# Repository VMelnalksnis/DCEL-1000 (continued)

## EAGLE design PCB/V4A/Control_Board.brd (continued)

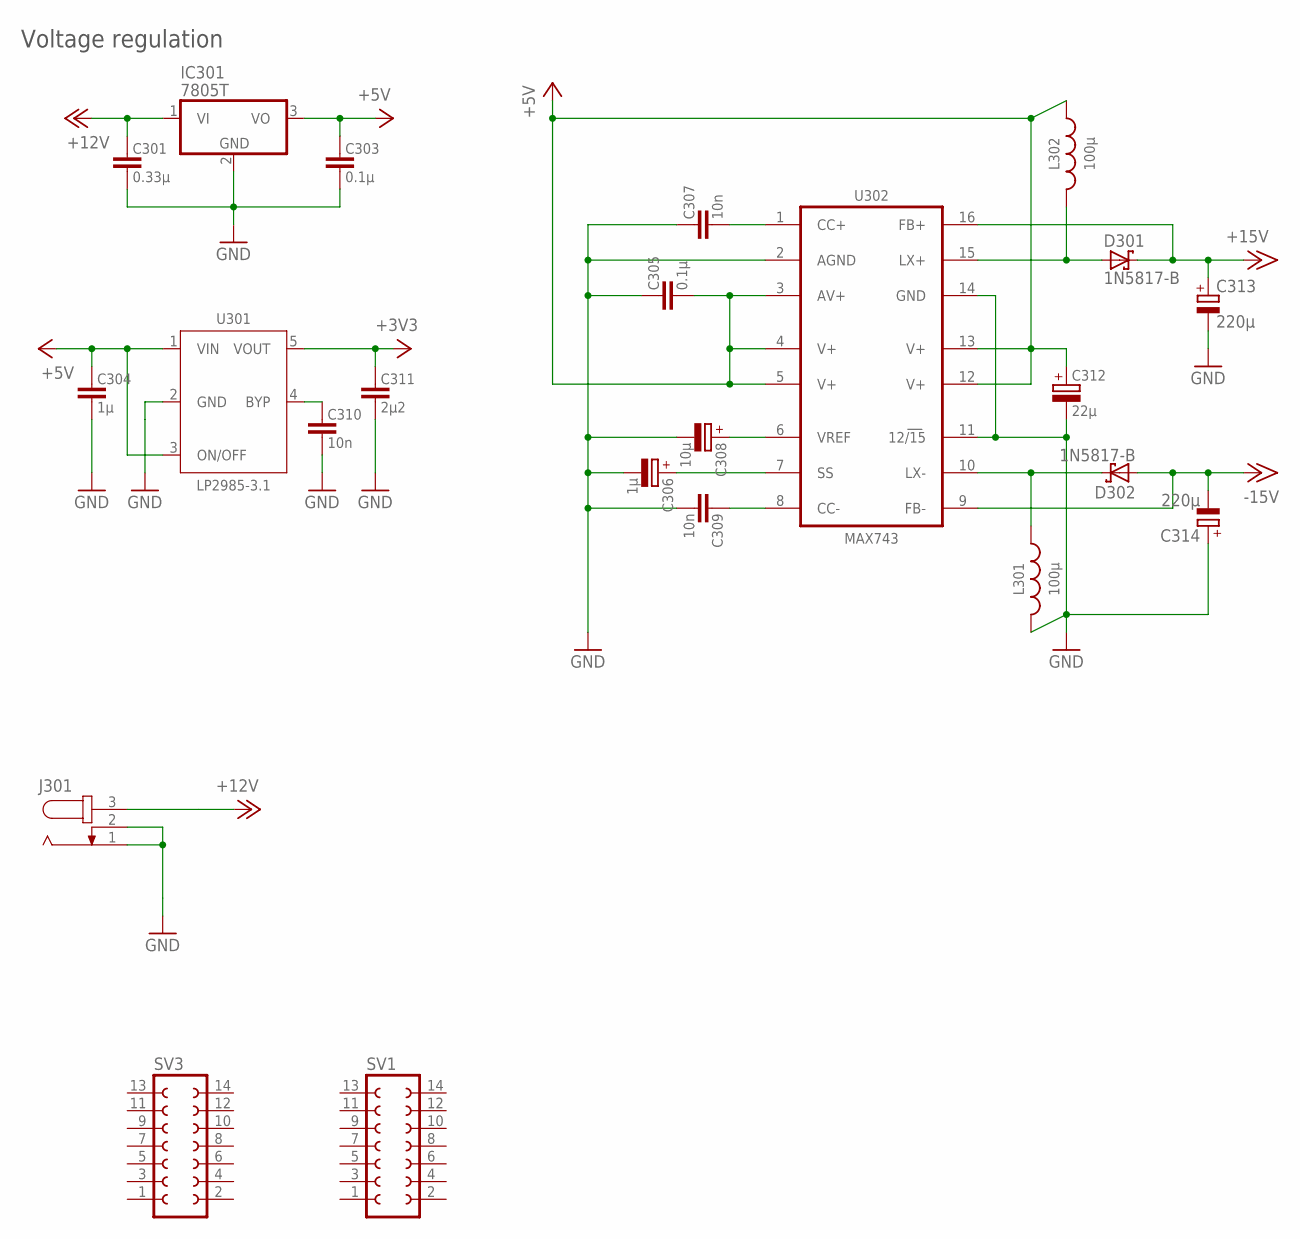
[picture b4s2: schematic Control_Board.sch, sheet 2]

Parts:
C301: 0.33µ; C3216
C303, C305: 0.1µ; C3216
C304: 1µ; C3216
C306: 1µ; CT3216
C307, C309, C310: 10n; C3216
C308: 10µ; CT6032
C311: 2µ2; C3216
C312: 22µ; CT6032
C313, C314: 220µ; E3,5-10
D301, D302: 1N5817-B; DO41-7.6
IC301: 7805T; TO220H
J301: JACK-PLUG0; SPC4077
L301, L302: 100µ; SRN1060
SV1, SV3: FE07-2W
U301: LP2985-3.1; SOT23-5L
U302: MAX743; SO16W

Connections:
+3V3: C311.1, U301.5 (VOUT); also elsewhere on the board
+5V: C303.1, C304.1, C305.2, C312.+, IC301.3 (VO), L302.1, U301.1 (VIN), U301.3 (ON/OFF), U302.3 (AV+), U302.4 (V+), U302.5 (V+), U302.12 (V+), U302.13 (V+); also elsewhere on the board
+12V: C301.1, IC301.1 (VI), J301.3
+15V: C313.+, D301.C, U302.16 (FB+); also elsewhere on the board
-15V: C314.-, D302.A, U302.9 (FB-); also elsewhere on the board
GND: C301.2, C303.2, C304.2, C305.1, C306.-, C307.1, C308.-, C309.2, C310.2, C311.2, C312.-, C313.-, C314.+, IC301.2 (GND), J301.1, J301.2, L301.2, U301.2 (GND), U302.2 (AGND), U302.11 (12/15), U302.14 (GND); also elsewhere on the board
unnamed: C310.1, U301.4 (BYP)
unnamed: C309.1, U302.8 (CC-)
unnamed: C306.+, U302.7 (SS)
unnamed: C307.2, U302.1 (CC+)
unnamed: D301.A, L302.2, U302.15 (LX+)
unnamed: D302.C, L301.1, U302.10 (LX-)
VREF2: C308.+, U302.6 (VREF)

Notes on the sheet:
Voltage regulation

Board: 2 copper layers, 53 parts (0 on the bottom side), 32 nets, no tracks yet.

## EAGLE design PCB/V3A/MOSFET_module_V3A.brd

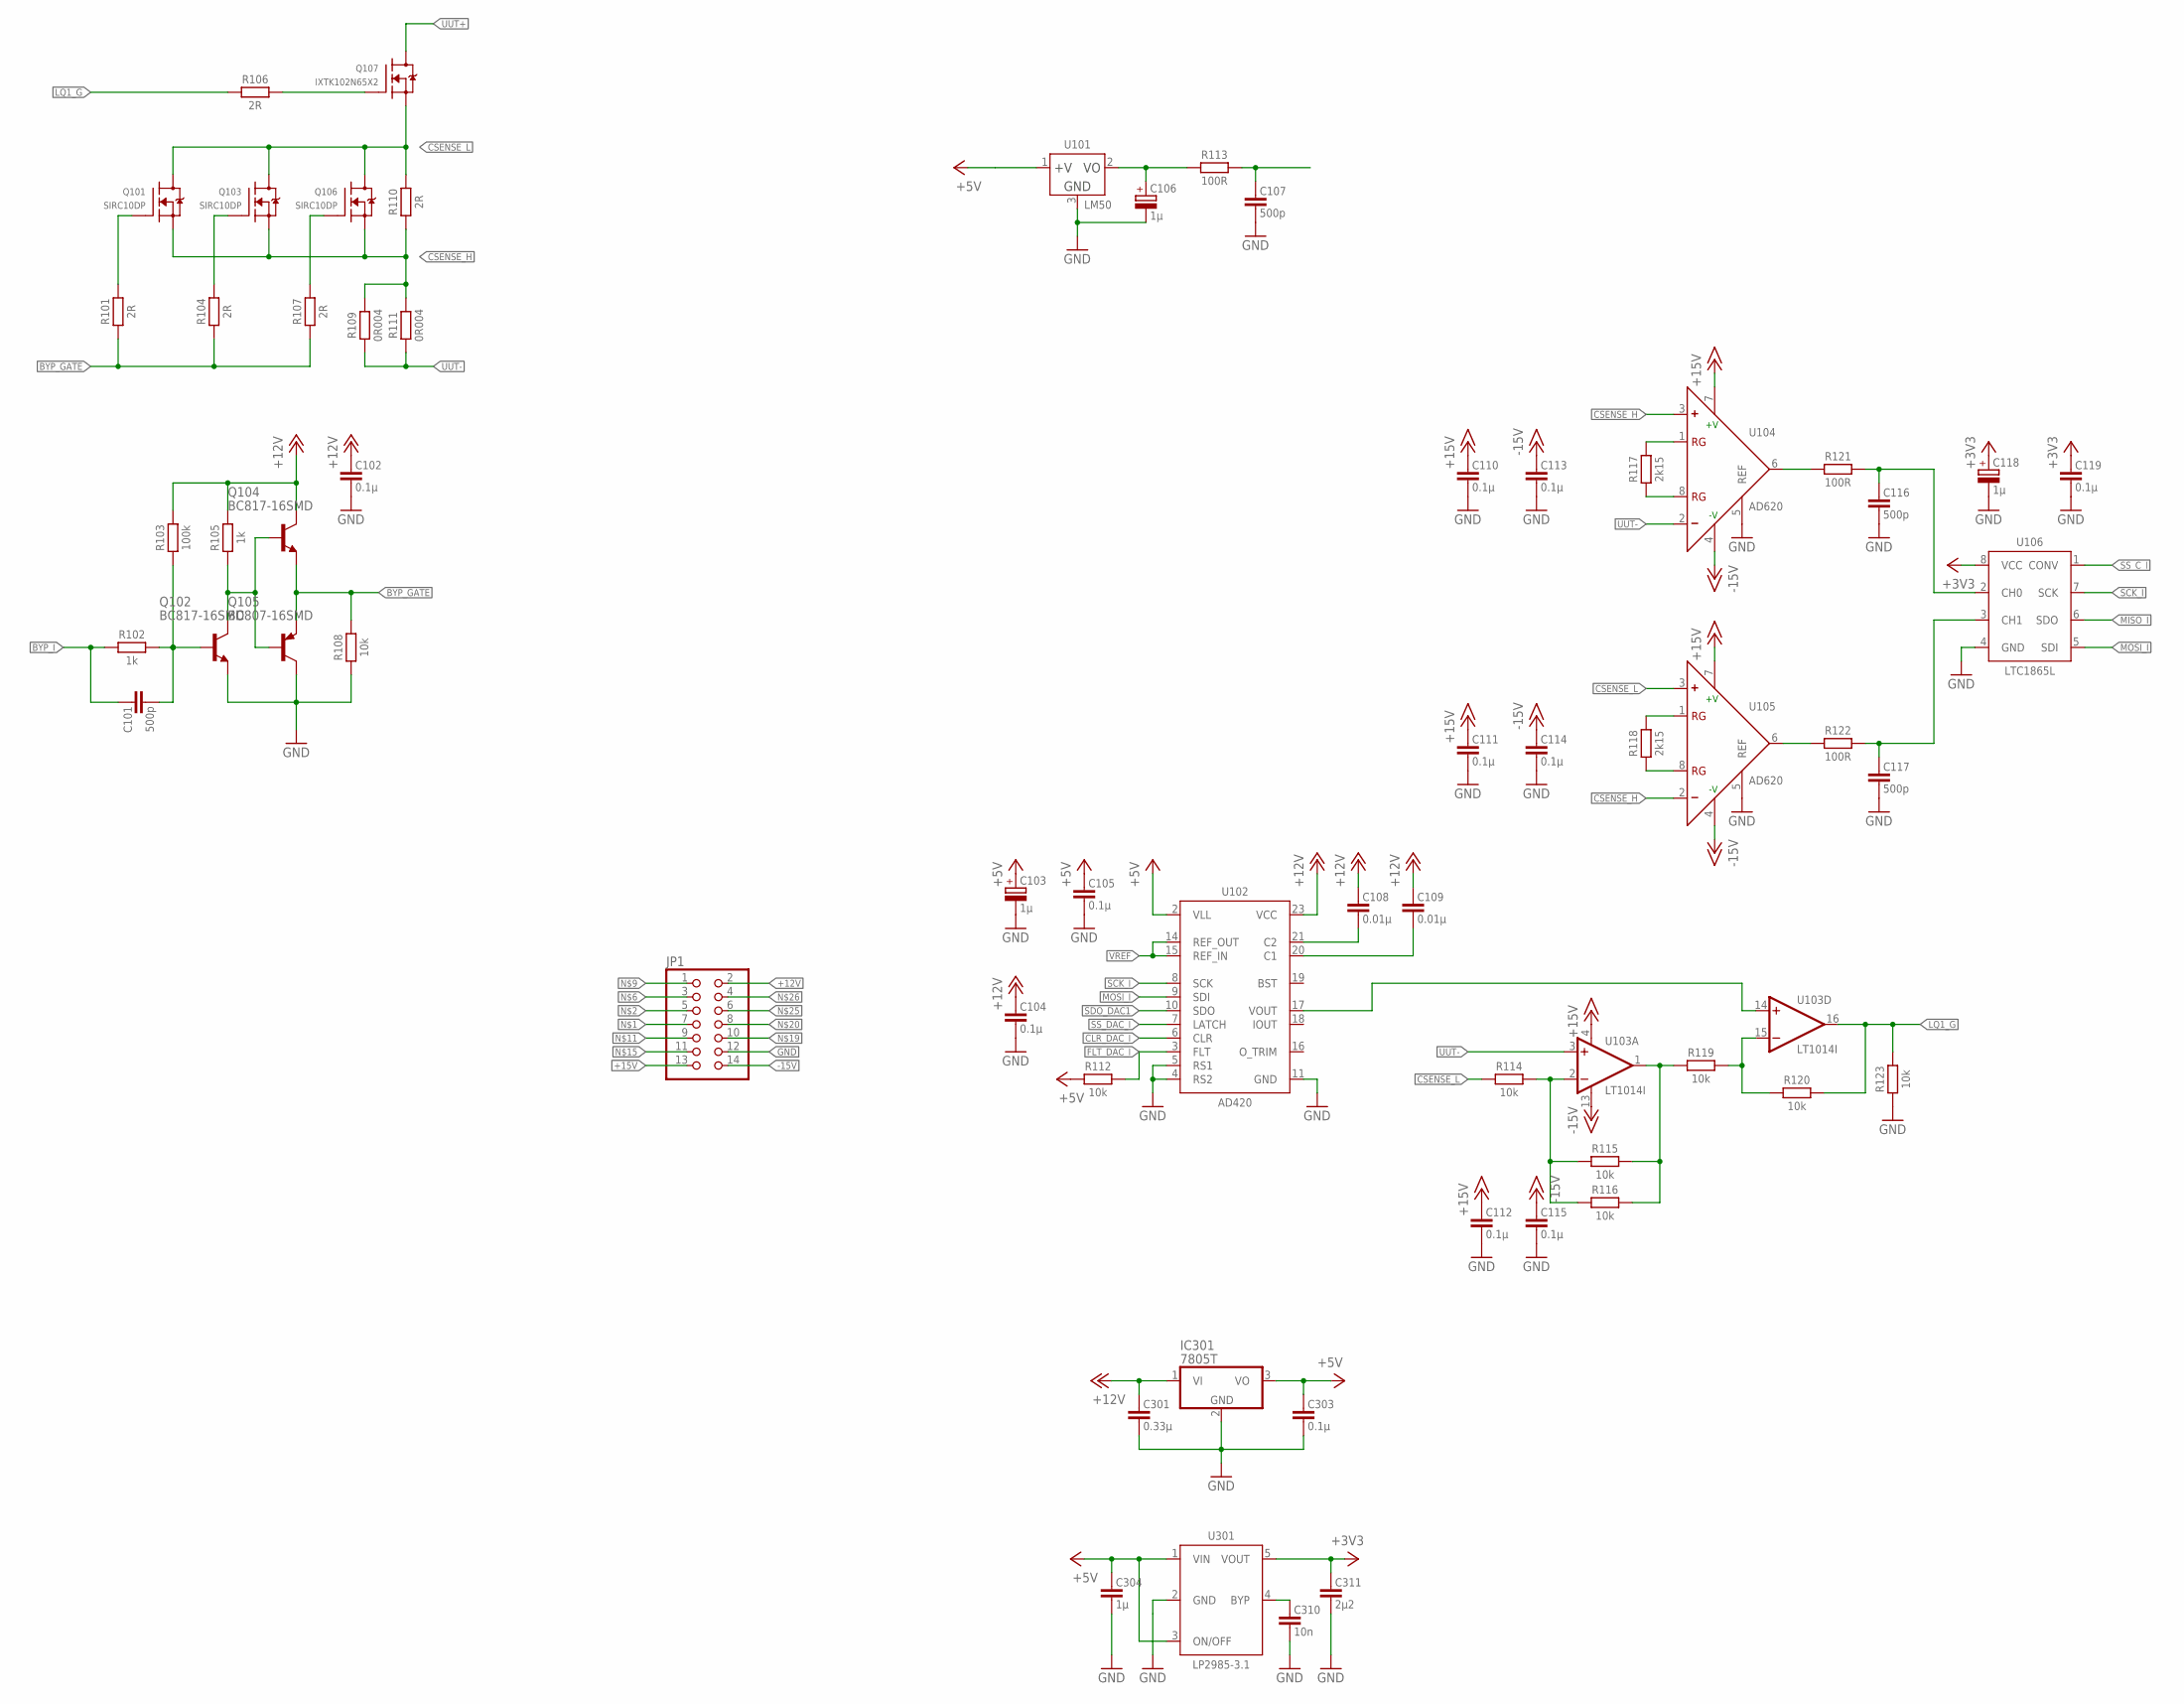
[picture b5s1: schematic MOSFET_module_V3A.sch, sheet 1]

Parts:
C101, C107, C116, C117: 500p; C1608
C102, C104, C105, C110, C111, C112, C113, C114, C115, C119, C303: 0.1µ; C3216
C103, C106, C118: 1µ; CT3216
C108, C109: 0.01µ; C3216
C301: 0.33µ; C3216
C304: 1µ; C3216
C310: 10n; C3216
C311: 2µ2; C3216
IC301: 7805T; TO220H
JP1: PINHD-2X7; 2X07
Q101, Q103, Q106: SIRC10DP; POWERPAK-SO-8
Q102, Q104: BC817-16SMD; SOT23-BEC
Q105: BC807-16SMD; SOT23-BEC
Q107: IXTK102N65X2; TO-264P-V
R101, R104, R106, R107, R110: 2R; R3216W
R102, R105: 1k; R1608
R103: 100k; R1608
R108, R112, R114, R115, R116, R119, R120, R123: 10k; R1608
R109, R111: 0R004; R6332W
R113, R121, R122: 100R; R2012W
R117, R118: 2k15; R2012W
U101: LM50; SOT23W
U102: AD420; SO24W
U103: LT1014I; SO16W
U104, U105: AD620; SO8
U106: LTC1865L; SO8
U301: LP2985-3.1; SOT23-5L

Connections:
+3V3: C118.+, C119.1, C311.1, U106.8 (VCC), U301.5 (VOUT)
+5V: C103.+, C105.1, C303.1, C304.1, IC301.3 (VO), R112.1, U101.1 (+V), U102.2 (VLL), U301.1 (VIN), U301.3 (ON/OFF); also elsewhere on the board
+12V: C102.1, C104.1, C108.1, C109.1, C301.1, IC301.1 (VI), JP1.2, Q104.C, R103.2, R105.2, U102.23 (VCC)
+15V: C110.1, C111.1, C112.1, JP1.13, U103.4 (V+), U104.7 (+V), U105.7 (+V)
-15V: C113.1, C114.1, C115.1, JP1.14, U103.13 (V-), U104.4 (-V), U105.4 (-V)
BYP_GATE: Q104.E, Q105.E, R101.1, R104.1, R107.1, R108.2
BYP_I: C101.1, R102.1
CLR_DAC_I: U102.6 (CLR)
CSENSE_H: Q101.1 (S), Q101.2 (S), Q101.3 (S), Q103.1 (S), Q103.2 (S), Q103.3 (S), Q106.1 (S), Q106.2 (S), Q106.3 (S), R109.2, R110.1, R111.2, U104.3 (+), U105.2 (-)
CSENSE_L: Q101.5 (D), Q103.5 (D), Q106.5 (D), Q107.3 (S), R110.2, R114.1, U105.3 (+)
DAC_VOUT: U102.17 (VOUT), U103.14 (+IN)
FLT_DAC_I: R112.2, U102.3 (FLT)
GATE1: Q107.1 (G), R106.2
GND: C102.2, C103.-, C104.2, C105.2, C106.-, C107.2, C110.2, C111.2, C112.2, C113.2, C114.2, C115.2, C116.2, C117.2, C118.-, C119.2, C301.2, C303.2, C304.2, C310.2, C311.2, IC301.2 (GND), JP1.12, Q102.E, Q105.C, R108.1, R123.1, U101.3 (GND), U102.4 (RS2), U102.5 (RS1), U102.11 (GND), U104.5 (REF), U105.5 (REF), U106.4 (GND), U301.2 (GND); also elsewhere on the board
LBQ11_G: Q101.4 (G), R101.2
LBQ12_G: Q103.4 (G), R104.2
LBQ13_G: Q106.4 (G), R107.2
LQ1_G: R106.1, R120.2, R123.2, U103.16 (OUT)
MISO_I: U106.6 (SDO)
MOSI_I: U102.9 (SDI), U106.5 (SDI)
unnamed: C108.2, U102.21 (C2)
unnamed: C109.2, U102.20 (C1)
unnamed: Q102.C, Q104.B, Q105.B, R105.1
unnamed: C107.1, R113.2
unnamed: C101.2, Q102.B, R102.2, R103.1
unnamed: C310.1, U301.4 (BYP)
unnamed: R119.2, R120.1, U103.15 (-IN)
unnamed: R115.2, R116.2, R119.1, U103.1 (OUT)
unnamed: R114.2, R115.1, R116.1, U103.2 (-IN)
unnamed: C116.1, R121.2, U106.2 (CH0)
unnamed: C117.1, R122.2, U106.3 (CH1)
unnamed: R122.1, U105.6 (OUT)
unnamed: R121.1, U104.6 (OUT)
RG1_L3: R117.2, U104.1 (RG)
RG1_L4: R118.2, U105.1 (RG)
RG2_L3: R117.1, U104.8 (RG)
RG2_L4: R118.1, U105.8 (RG)
SCK_I: U102.8 (SCK), U106.7 (SCK)
SDO_DAC1: U102.10 (SDO)
SS_C_I: U106.1 (CONV)
SS_DAC_I: U102.7 (LATCH)
T1_OUT: C106.+, R113.1, U101.2 (VO)
UUT+: Q107.2 (D)
UUT-: R109.1, R111.1, U103.3 (+IN), U104.2 (-)
VREF: U102.14 (REF_OUT), U102.15 (REF_IN)

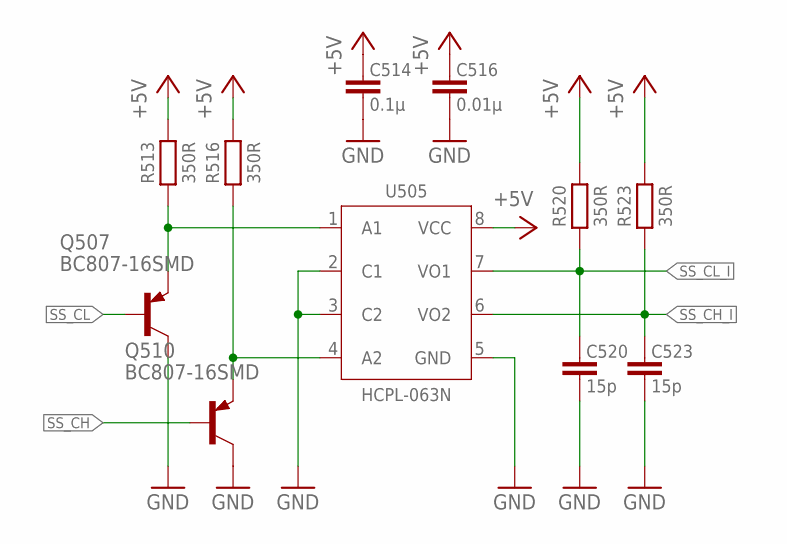
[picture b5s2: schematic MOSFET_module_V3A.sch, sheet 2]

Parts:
C514: 0.1µ; C3216
C516: 0.01µ; C3216
C520, C523: 15p; C1608
Q507, Q510: BC807-16SMD; SOT23-BEC
R513, R516, R520, R523: 350R; R1608
U505: HCPL-063N; SO8

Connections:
+5V: C514.1, C516.1, R513.2, R516.2, R520.2, R523.2, U505.8 (VCC); also elsewhere on the board
GND: C514.2, C516.2, C520.2, C523.2, Q507.C, Q510.C, U505.2 (C1), U505.3 (C2), U505.5 (GND); also elsewhere on the board
unnamed: Q507.E, R513.1, U505.1 (A1)
unnamed: Q510.E, R516.1, U505.4 (A2)
SS_CH: Q510.B
SS_CH_I: C523.1, R523.1, U505.6 (VO2)
SS_CL: Q507.B
SS_CL_I: C520.1, R520.1, U505.7 (VO1)

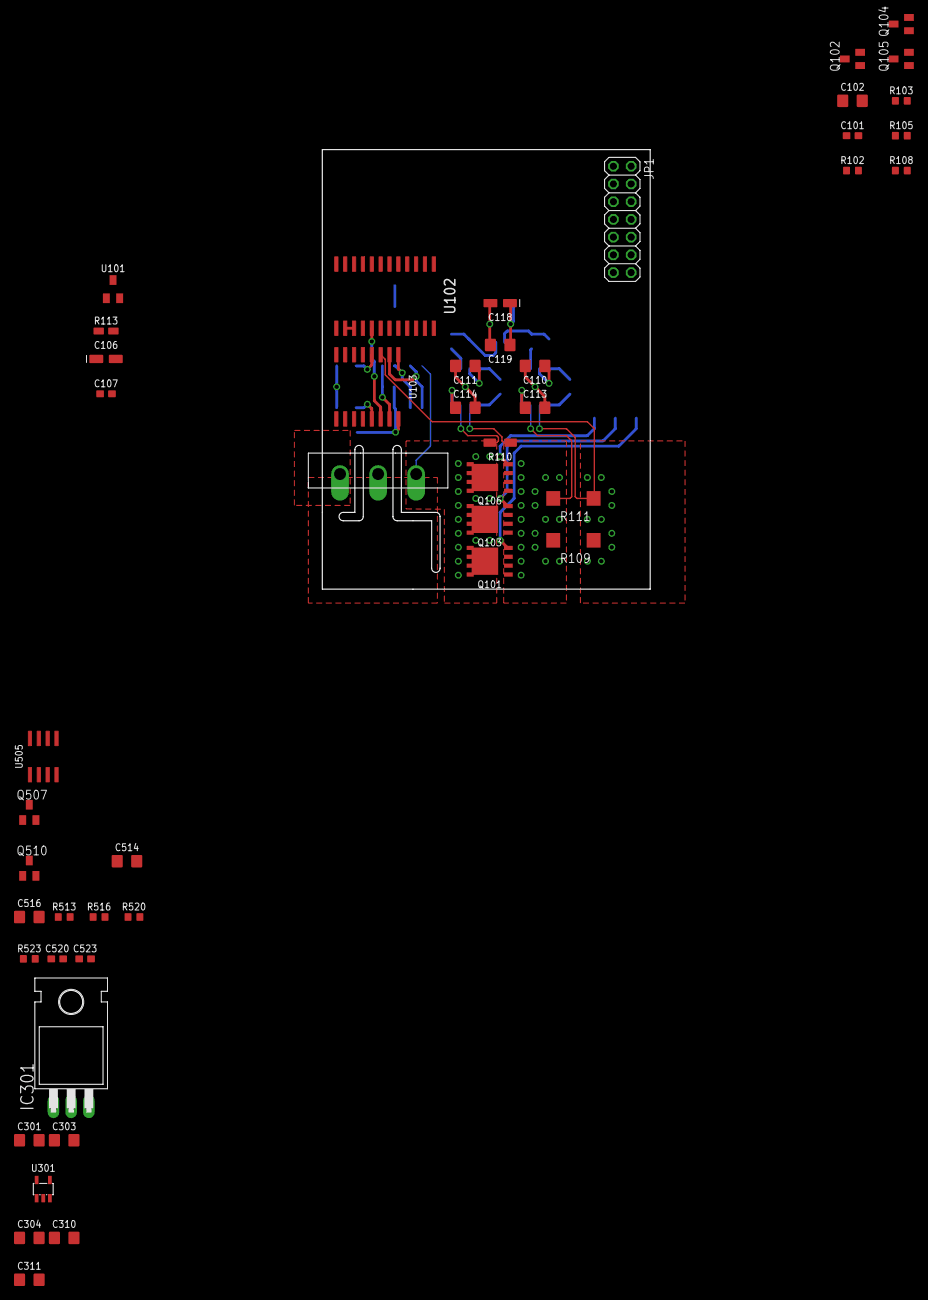
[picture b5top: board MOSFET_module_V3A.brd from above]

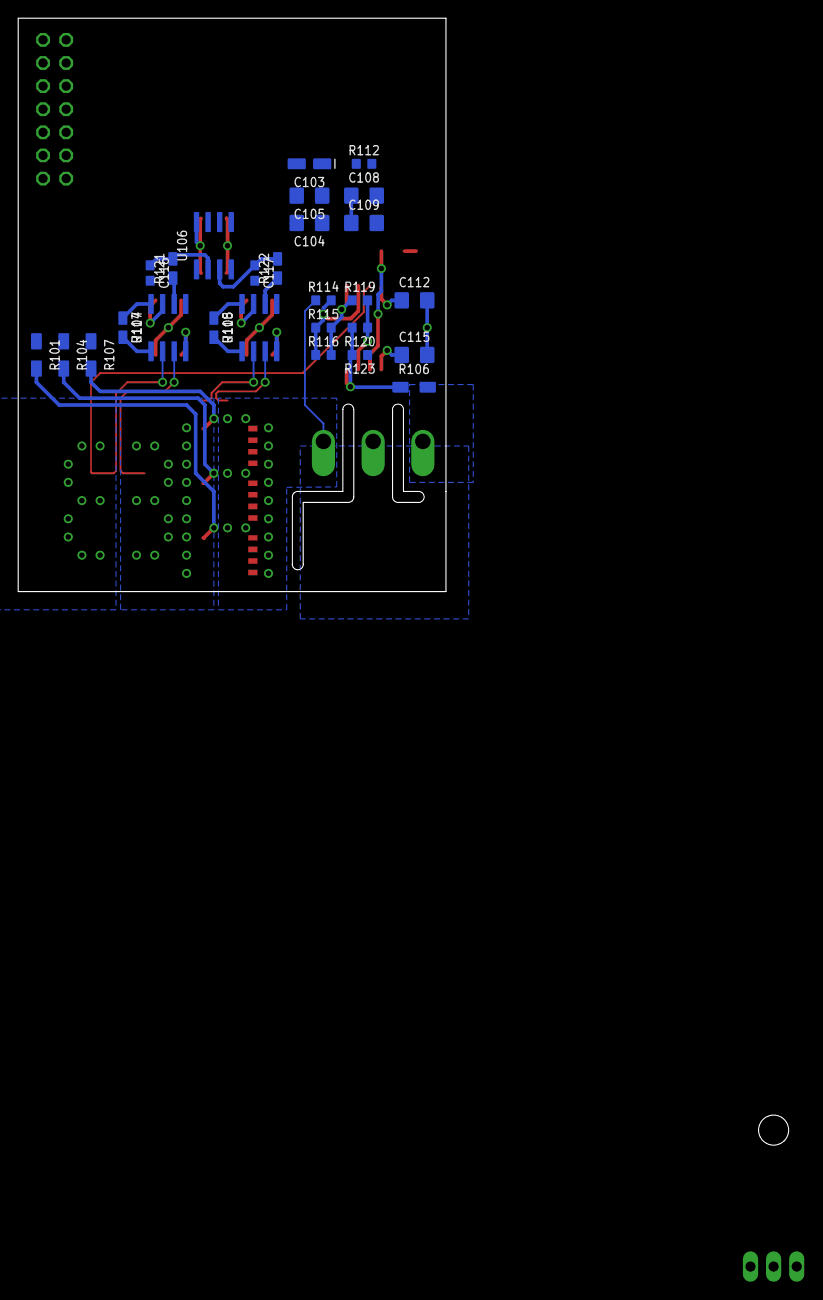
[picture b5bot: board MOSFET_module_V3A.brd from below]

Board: 4 copper layers, 47.0 x 63.0 mm, 74 parts (27 on the bottom side), 43 nets.

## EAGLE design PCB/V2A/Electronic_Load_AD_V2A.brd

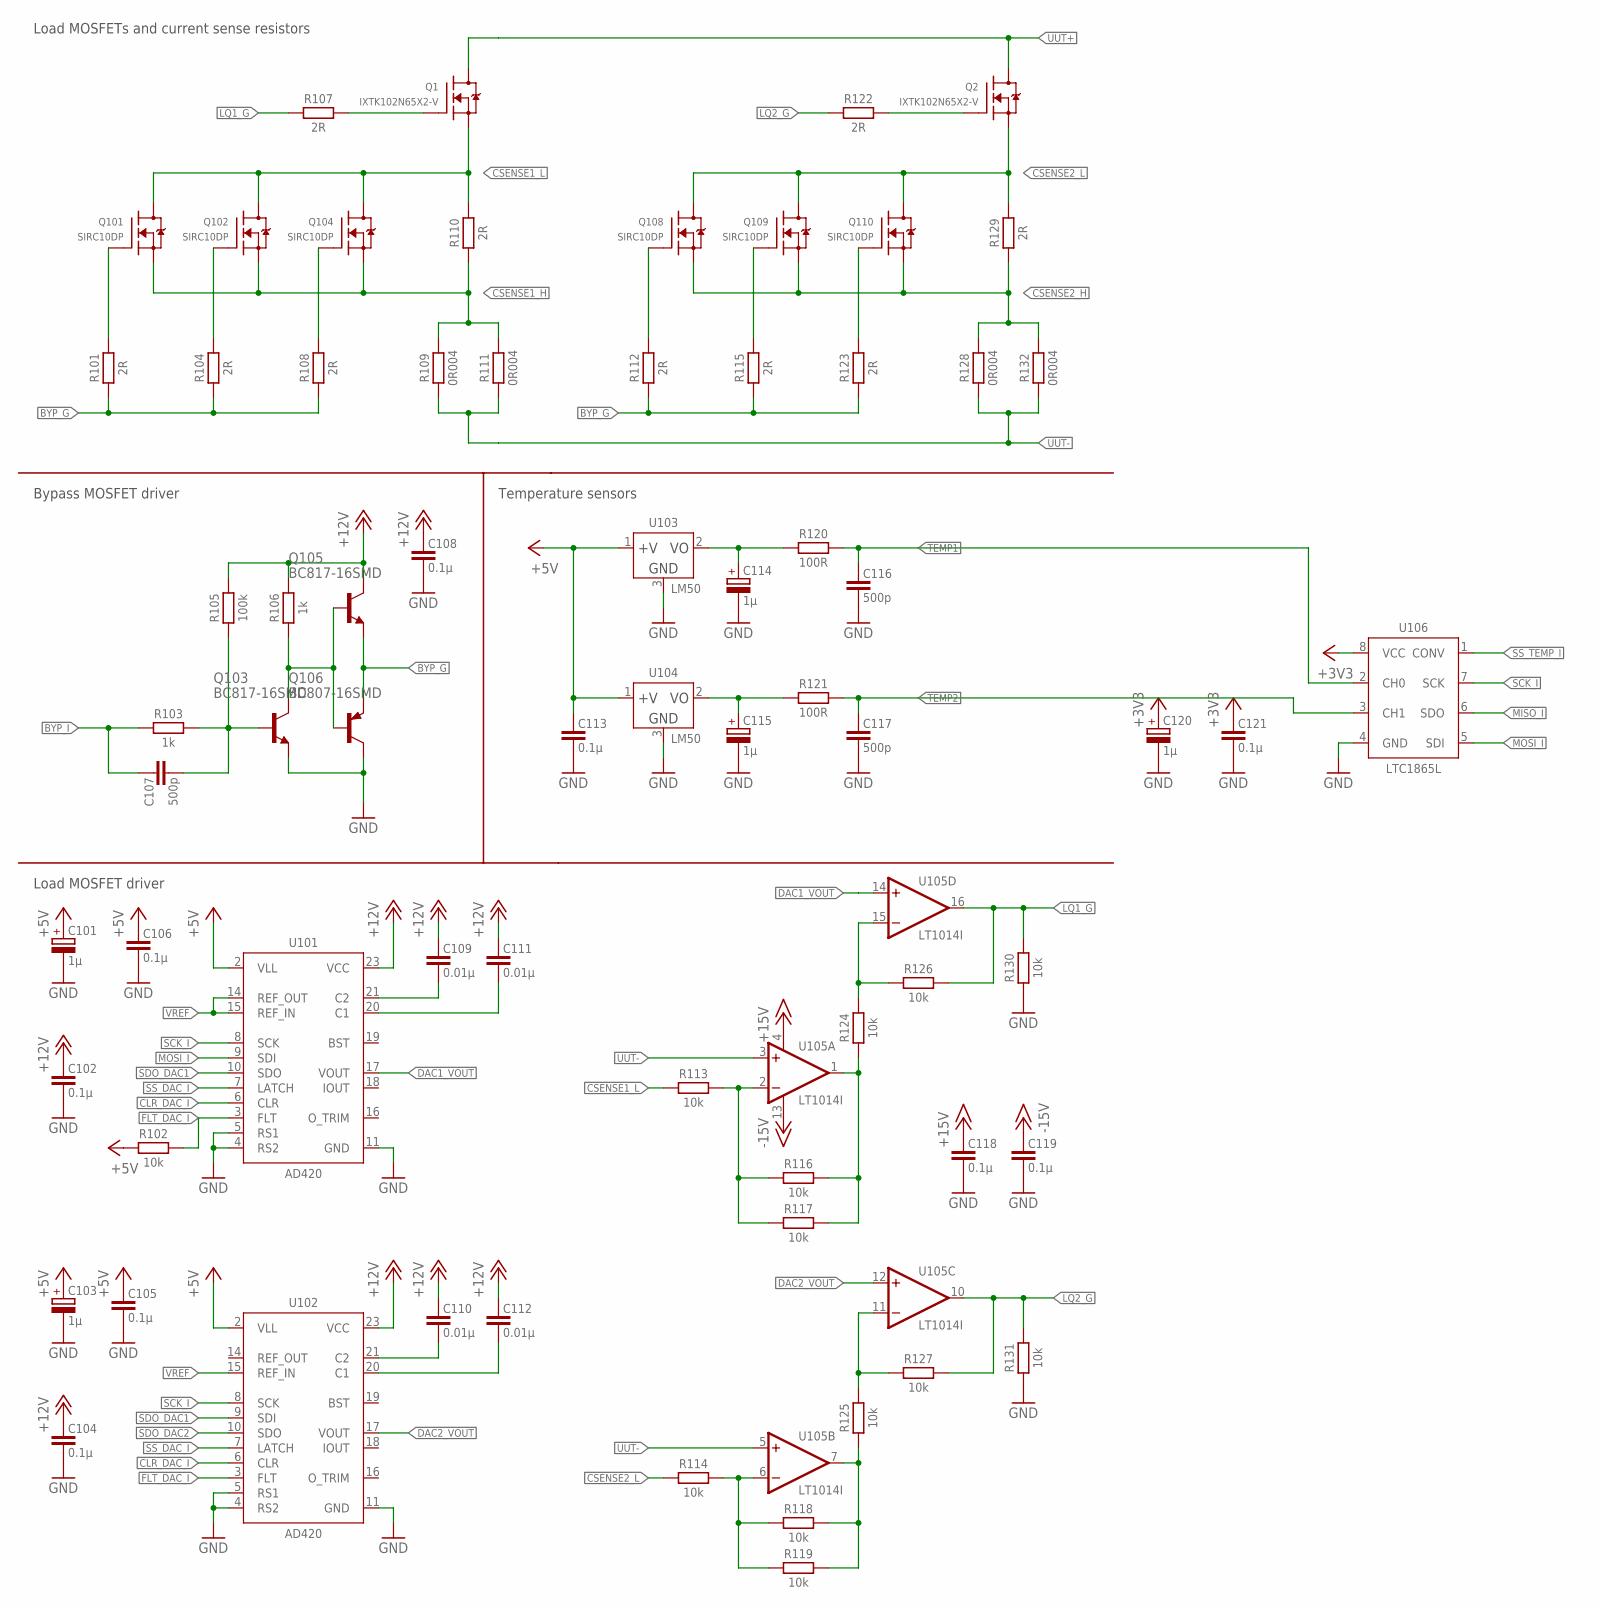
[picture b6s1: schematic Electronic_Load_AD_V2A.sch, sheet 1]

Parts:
C101, C103, C114, C115, C120: 1µ; CT3216
C102, C104, C105, C106, C108, C113, C118, C119, C121: 0.1µ; C3216
C107, C116, C117: 500p; C1608
C109, C110, C111, C112: 0.01µ; C3216
Q1, Q2: IXTK102N65X2-V; TO-264P-V
Q101, Q102, Q104, Q108, Q109, Q110: SIRC10DP; POWERPAK-SO-8
Q103, Q105: BC817-16SMD; SOT23-BEC
Q106: BC807-16SMD; SOT23-BEC
R101, R104, R107, R108, R112, R115, R122, R123: 2R; R2012W
R102, R113, R114, R116, R117, R118, R119, R124, R125, R126, R127, R130, R131: 10k; R1608
R103, R106: 1k; R1608
R105: 100k; R1608
R109, R111, R128, R132: 0R004; R6332W
R110, R129: 2R; R3216W
R120, R121: 100R; R2012W
U101, U102: AD420; SO24W
U103, U104: LM50; SOT23W
U105: LT1014I; SO16W
U106: LTC1865L; SO8

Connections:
+3V3: C120.+, C121.1, U106.8 (VCC); also elsewhere on the board
+5V: C101.+, C103.+, C105.1, C106.1, C113.1, R102.1, U101.2 (VLL), U102.2 (VLL), U103.1 (+V), U104.1 (+V); also elsewhere on the board
+12V: C102.1, C104.1, C108.1, C109.1, C110.1, C111.1, C112.1, Q105.C, R105.2, R106.2, U101.23 (VCC), U102.23 (VCC); also elsewhere on the board
+15V: C118.1, U105.4 (V+); also elsewhere on the board
-15V: C119.1, U105.13 (V-); also elsewhere on the board
BYP_G: Q105.E, Q106.E, R101.1, R104.1, R108.1, R112.1, R115.1, R123.1
BYP_I: C107.1, R103.1; also elsewhere on the board
CLR_DAC_I: U101.6 (CLR), U102.6 (CLR); also elsewhere on the board
CSENSE1_H: Q101.1 (S), Q101.2 (S), Q101.3 (S), Q102.1 (S), Q102.2 (S), Q102.3 (S), Q104.1 (S), Q104.2 (S), Q104.3 (S), R109.2, R110.1, R111.2; also elsewhere on the board
CSENSE1_L: Q1.3 (S), Q101.5 (D), Q102.5 (D), Q104.5 (D), R110.2, R113.1; also elsewhere on the board
CSENSE2_H: Q108.1 (S), Q108.2 (S), Q108.3 (S), Q109.1 (S), Q109.2 (S), Q109.3 (S), Q110.1 (S), Q110.2 (S), Q110.3 (S), R128.2, R129.1, R132.2; also elsewhere on the board
CSENSE2_L: Q2.3 (S), Q108.5 (D), Q109.5 (D), Q110.5 (D), R114.1, R129.2; also elsewhere on the board
DAC1_VOUT: U101.17 (VOUT), U105.14 (+IN)
DAC2_VOUT: U102.17 (VOUT), U105.12 (+IN)
FLT_DAC_I: R102.2, U101.3 (FLT), U102.3 (FLT); also elsewhere on the board
GATE1: Q1.1 (G), R107.2; also elsewhere on the board
GATE2: Q2.1 (G), R122.2; also elsewhere on the board
GND: C101.-, C102.2, C103.-, C104.2, C105.2, C106.2, C108.2, C113.2, C114.-, C115.-, C116.2, C117.2, C118.2, C119.2, C120.-, C121.2, Q103.E, Q106.C, R130.1, R131.1, U101.4 (RS2), U101.5 (RS1), U101.11 (GND), U102.4 (RS2), U102.5 (RS1), U102.11 (GND), U103.3 (GND), U104.3 (GND), U106.4 (GND); also elsewhere on the board
LBQ11_G: Q101.4 (G), R101.2
LBQ12_G: Q102.4 (G), R104.2
LBQ13_G: Q104.4 (G), R108.2
LBQ21_G: Q108.4 (G), R112.2
LBQ22_G: Q109.4 (G), R115.2
LBQ23_G: Q110.4 (G), R123.2
LQ1_G: R107.1, R126.2, R130.2, U105.16 (OUT)
LQ2_G: R122.1, R127.2, R131.2, U105.10 (OUT)
MISO_I: U106.6 (SDO); also elsewhere on the board
MOSI_I: U101.9 (SDI), U106.5 (SDI); also elsewhere on the board
unnamed: C109.2, U101.21 (C2)
unnamed: C111.2, U101.20 (C1)
unnamed: Q103.C, Q105.B, Q106.B, R106.1
unnamed: C110.2, U102.21 (C2)
unnamed: C112.2, U102.20 (C1)
unnamed: C107.2, Q103.B, R103.2, R105.1
unnamed: R125.2, R127.1, U105.11 (-IN)
unnamed: R124.2, R126.1, U105.15 (-IN)
unnamed: R116.2, R117.2, R124.1, U105.1 (OUT)
unnamed: R113.2, R116.1, R117.1, U105.2 (-IN)
unnamed: R114.2, R118.1, R119.1, U105.6 (-IN)
unnamed: R118.2, R119.2, R125.1, U105.7 (OUT)
SCK_I: U101.8 (SCK), U102.8 (SCK), U106.7 (SCK); also elsewhere on the board
SDO_DAC1: U101.10 (SDO), U102.9 (SDI)
SDO_DAC2: U102.10 (SDO)
SS_DAC_I: U101.7 (LATCH), U102.7 (LATCH); also elsewhere on the board
SS_TEMP_I: U106.1 (CONV); also elsewhere on the board
T1_OUT: C114.+, R120.1, U103.2 (VO); also elsewhere on the board
T2_OUT: C115.+, R121.1, U104.2 (VO); also elsewhere on the board
TEMP1: C116.1, R120.2, U106.2 (CH0)
TEMP2: C117.1, R121.2, U106.3 (CH1)
UUT+: Q1.2 (D), Q2.2 (D)
UUT-: R109.1, R111.1, R128.1, R132.1, U105.3 (+IN), U105.5 (+IN); also elsewhere on the board
VREF: U101.14 (REF_OUT), U101.15 (REF_IN), U102.15 (REF_IN)

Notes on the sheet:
Load MOSFETs and current sense resistors
Bypass MOSFET driver
Temperature sensors
Load MOSFET driver

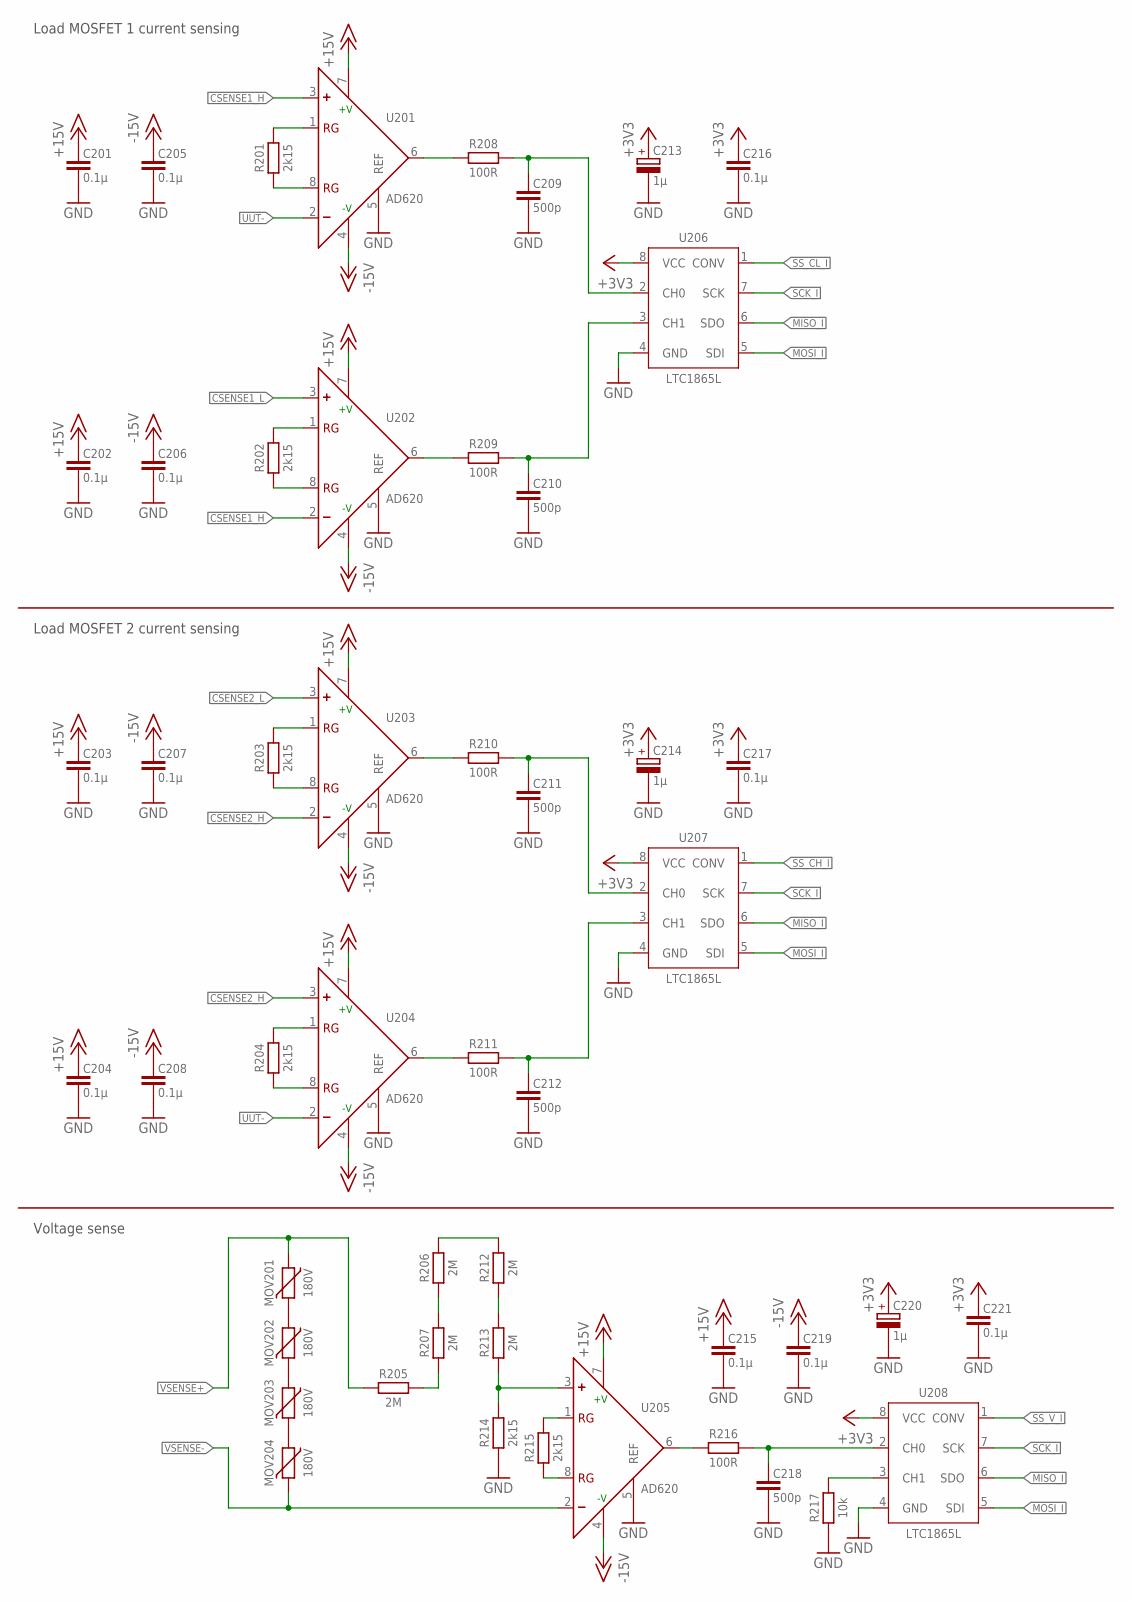
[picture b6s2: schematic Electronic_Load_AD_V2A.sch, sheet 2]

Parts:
C201, C202, C203, C204, C205, C206, C207, C208, C215, C216, C217, C219, C221: 0.1µ; C3216
C209, C210, C211, C212, C218: 500p; C1608
C213, C214, C220: 1µ; CT3216
MOV201, MOV202, MOV203, MOV204: 180V; R3225W
R201, R202, R203, R204, R214, R215: 2k15; R2012W
R205, R206, R207, R212, R213: 2M; R3216W
R208, R209, R210, R211, R216: 100R; R2012W
R217: 10k; R1608
U201, U202, U203, U204, U205: AD620; SO8
U206, U207, U208: LTC1865L; SO8

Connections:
+3V3: C213.+, C214.+, C216.1, C217.1, C220.+, C221.1, U206.8 (VCC), U207.8 (VCC), U208.8 (VCC); also elsewhere on the board
+15V: C201.1, C202.1, C203.1, C204.1, C215.1, U201.7 (+V), U202.7 (+V), U203.7 (+V), U204.7 (+V), U205.7 (+V); also elsewhere on the board
-15V: C205.1, C206.1, C207.1, C208.1, C219.1, U201.4 (-V), U202.4 (-V), U203.4 (-V), U204.4 (-V), U205.4 (-V); also elsewhere on the board
CSENSE1_H: U201.3 (+), U202.2 (-); also elsewhere on the board
CSENSE1_L: U202.3 (+); also elsewhere on the board
CSENSE2_H: U203.2 (-), U204.3 (+); also elsewhere on the board
CSENSE2_L: U203.3 (+); also elsewhere on the board
GND: C201.2, C202.2, C203.2, C204.2, C205.2, C206.2, C207.2, C208.2, C209.2, C210.2, C211.2, C212.2, C213.-, C214.-, C215.2, C216.2, C217.2, C218.2, C219.2, C220.-, C221.2, R214.1, R217.1, U201.5 (REF), U202.5 (REF), U203.5 (REF), U204.5 (REF), U205.5 (REF), U206.4 (GND), U207.4 (GND), U208.4 (GND); also elsewhere on the board
MISO_I: U206.6 (SDO), U207.6 (SDO), U208.6 (SDO); also elsewhere on the board
MOSI_I: U206.5 (SDI), U207.5 (SDI), U208.5 (SDI); also elsewhere on the board
unnamed: MOV201.2, MOV202.1
unnamed: MOV202.2, MOV203.1
unnamed: R210.1, U203.6 (OUT)
unnamed: C211.1, R210.2, U207.2 (CH0)
unnamed: R211.1, U204.6 (OUT)
unnamed: C212.1, R211.2, U207.3 (CH1)
unnamed: C209.1, R208.2, U206.2 (CH0)
unnamed: C210.1, R209.2, U206.3 (CH1)
unnamed: R209.1, U202.6 (OUT)
unnamed: R208.1, U201.6 (OUT)
unnamed: R212.1, R213.2
unnamed: R206.2, R212.2
unnamed: R206.1, R207.2
unnamed: R205.2, R207.1
unnamed: R213.1, R214.2, U205.3 (+)
unnamed: C218.1, R216.2, U208.2 (CH0)
unnamed: R216.1, U205.6 (OUT)
unnamed: MOV203.2, MOV204.1
unnamed: R217.2, U208.3 (CH1)
RG1_H4: R203.2, U203.1 (RG)
RG1_H5: R204.2, U204.1 (RG)
RG1_H6: R215.2, U205.1 (RG)
RG1_L3: R201.2, U201.1 (RG)
RG1_L4: R202.2, U202.1 (RG)
RG2_H4: R203.1, U203.8 (RG)
RG2_H5: R204.1, U204.8 (RG)
RG2_H6: R215.1, U205.8 (RG)
RG2_L3: R201.1, U201.8 (RG)
RG2_L4: R202.1, U202.8 (RG)
SCK_I: U206.7 (SCK), U207.7 (SCK), U208.7 (SCK); also elsewhere on the board
SS_CH_I: U207.1 (CONV); also elsewhere on the board
SS_CL_I: U206.1 (CONV); also elsewhere on the board
SS_V_I: U208.1 (CONV); also elsewhere on the board
UUT-: U201.2 (-), U204.2 (-); also elsewhere on the board
VSENSE+: MOV201.1, R205.1; also elsewhere on the board
VSENSE-: MOV204.2, U205.2 (-); also elsewhere on the board

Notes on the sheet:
Load MOSFET 2 current sensing
Load MOSFET 1 current sensing
Voltage sense

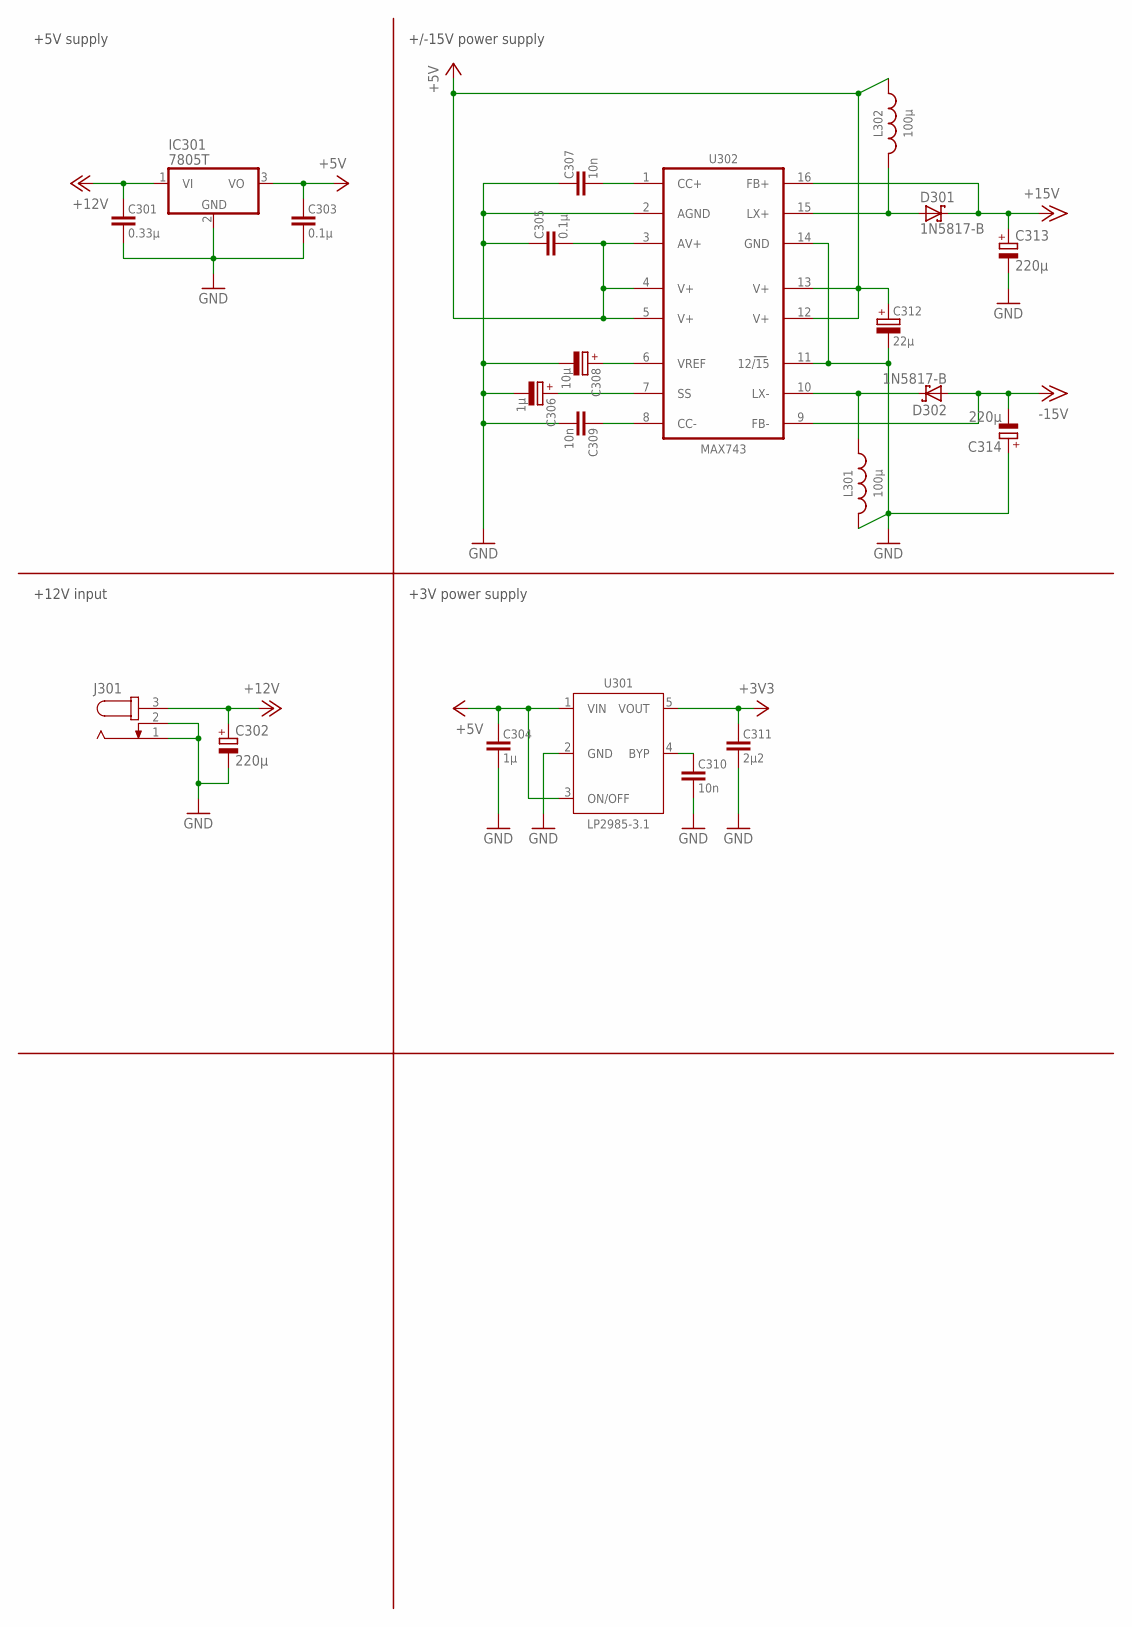
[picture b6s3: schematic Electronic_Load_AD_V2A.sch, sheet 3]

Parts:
C301: 0.33µ; C3216
C302, C313, C314: 220µ; E3,5-10
C303, C305: 0.1µ; C3216
C304: 1µ; C3216
C306: 1µ; CT3216
C307, C309, C310: 10n; C3216
C308: 10µ; CT6032
C311: 2µ2; C3216
C312: 22µ; CT6032
D301, D302: 1N5817-B; DO41-7.6
IC301: 7805T; TO220H
J301: JACK-PLUG0; SPC4077
L301, L302: 100µ; SRN1060
U301: LP2985-3.1; SOT23-5L
U302: MAX743; SO16W

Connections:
+3V3: C311.1, U301.5 (VOUT); also elsewhere on the board
+5V: C303.1, C304.1, C305.2, C312.+, IC301.3 (VO), L302.1, U301.1 (VIN), U301.3 (ON/OFF), U302.3 (AV+), U302.4 (V+), U302.5 (V+), U302.12 (V+), U302.13 (V+); also elsewhere on the board
+12V: C301.1, C302.+, IC301.1 (VI), J301.3; also elsewhere on the board
+15V: C313.+, D301.C, U302.16 (FB+); also elsewhere on the board
-15V: C314.-, D302.A, U302.9 (FB-); also elsewhere on the board
GND: C301.2, C302.-, C303.2, C304.2, C305.1, C306.-, C307.1, C308.-, C309.2, C310.2, C311.2, C312.-, C313.-, C314.+, IC301.2 (GND), J301.1, J301.2, L301.2, U301.2 (GND), U302.2 (AGND), U302.11 (12/15), U302.14 (GND); also elsewhere on the board
unnamed: C310.1, U301.4 (BYP)
unnamed: C309.1, U302.8 (CC-)
unnamed: C306.+, U302.7 (SS)
unnamed: C307.2, U302.1 (CC+)
unnamed: D301.A, L302.2, U302.15 (LX+)
unnamed: D302.C, L301.1, U302.10 (LX-)
VREF2: C308.+, U302.6 (VREF)

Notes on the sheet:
+/-15V power supply
+5V supply
+12V input
+3V power supply
